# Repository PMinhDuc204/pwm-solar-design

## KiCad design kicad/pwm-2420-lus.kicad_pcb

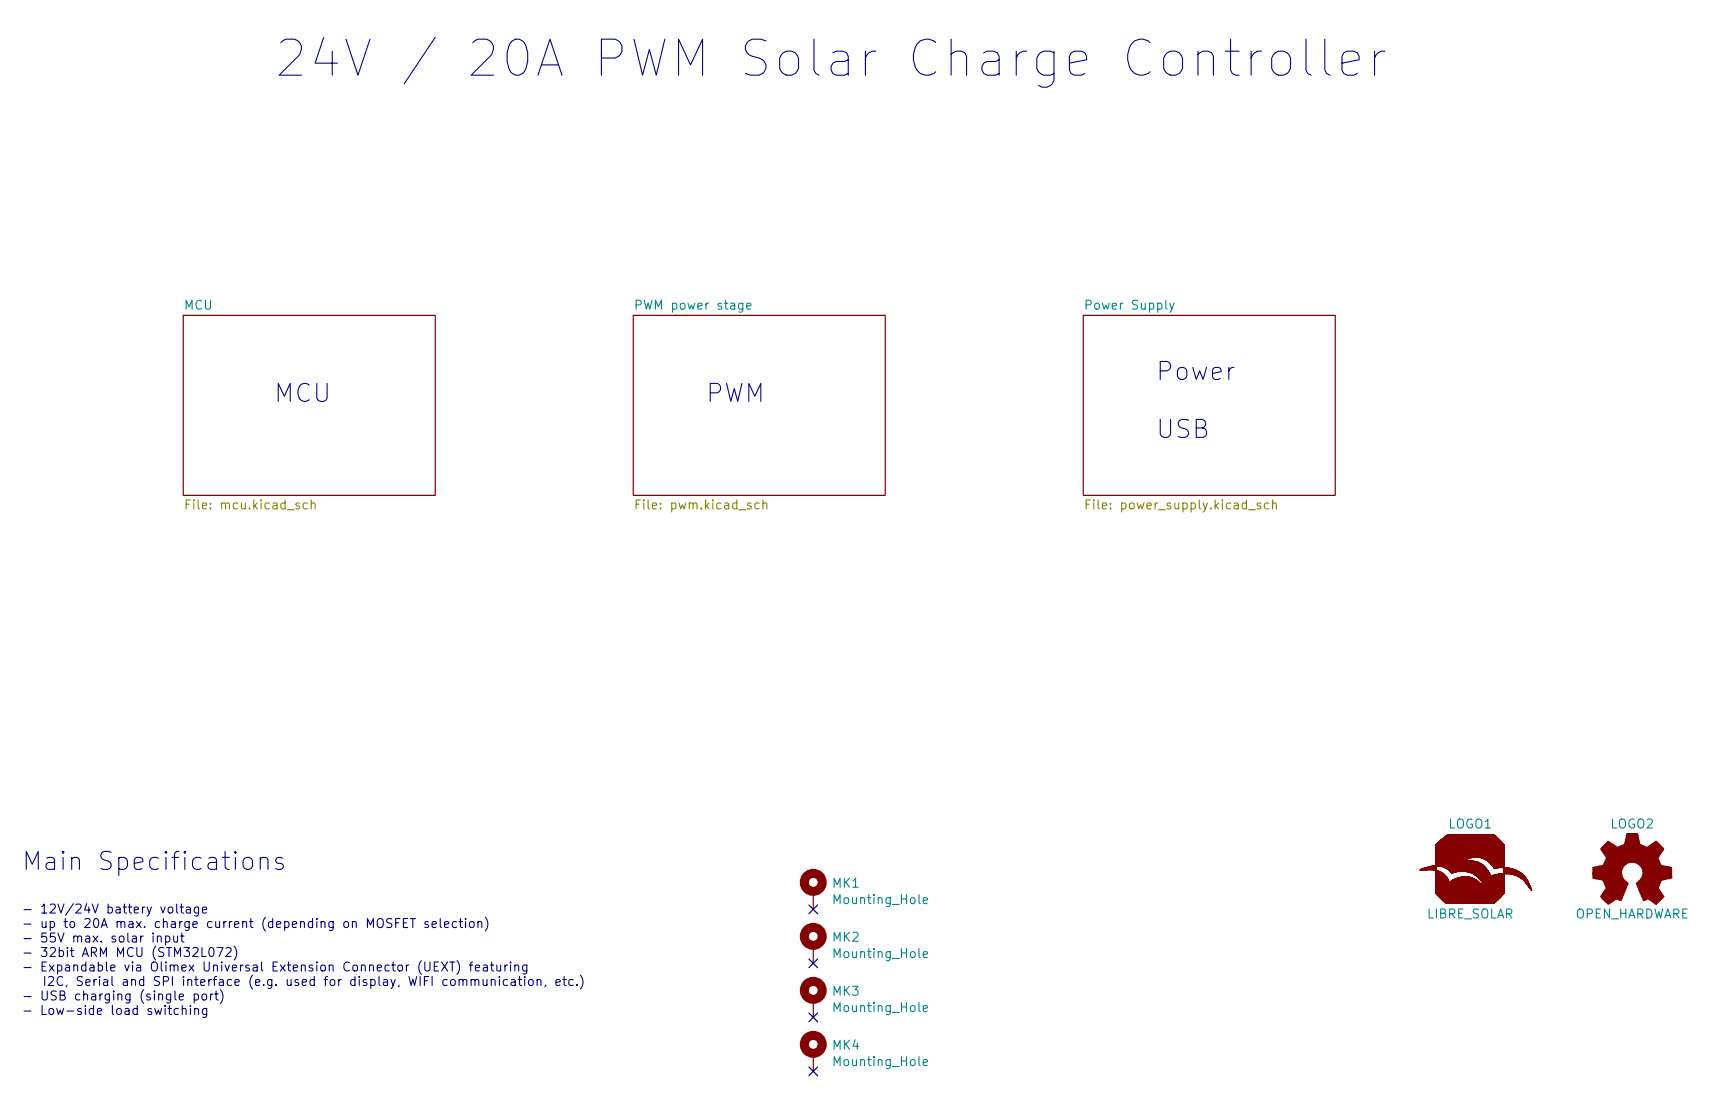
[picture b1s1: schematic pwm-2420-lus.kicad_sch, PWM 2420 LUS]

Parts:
LOGO1: LIBRE_SOLAR; LIBRESOLAR_LOGO
LOGO2: OPEN_HARDWARE; OSHW-Logo_5.7x6mm_SilkScreen
MK1, MK2, MK3, MK4: Mounting_Hole; MountingHole_3.2mm_M3_Pad

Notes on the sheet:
MCU
Main Specifications
24V / 20A PWM Solar Charge Controller
PWM
- 12V/24V battery voltage - up to 20A max. charge current (depending on MOSFET selection) - 55V max. solar input - 32bit ARM MCU (STM32L072) - Expandable via Olimex Universal Extension Connector (UEXT) featuring I2C, Serial and SPI interface (e.g. used for display, WIFI communication, etc.) - USB c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
Power USB

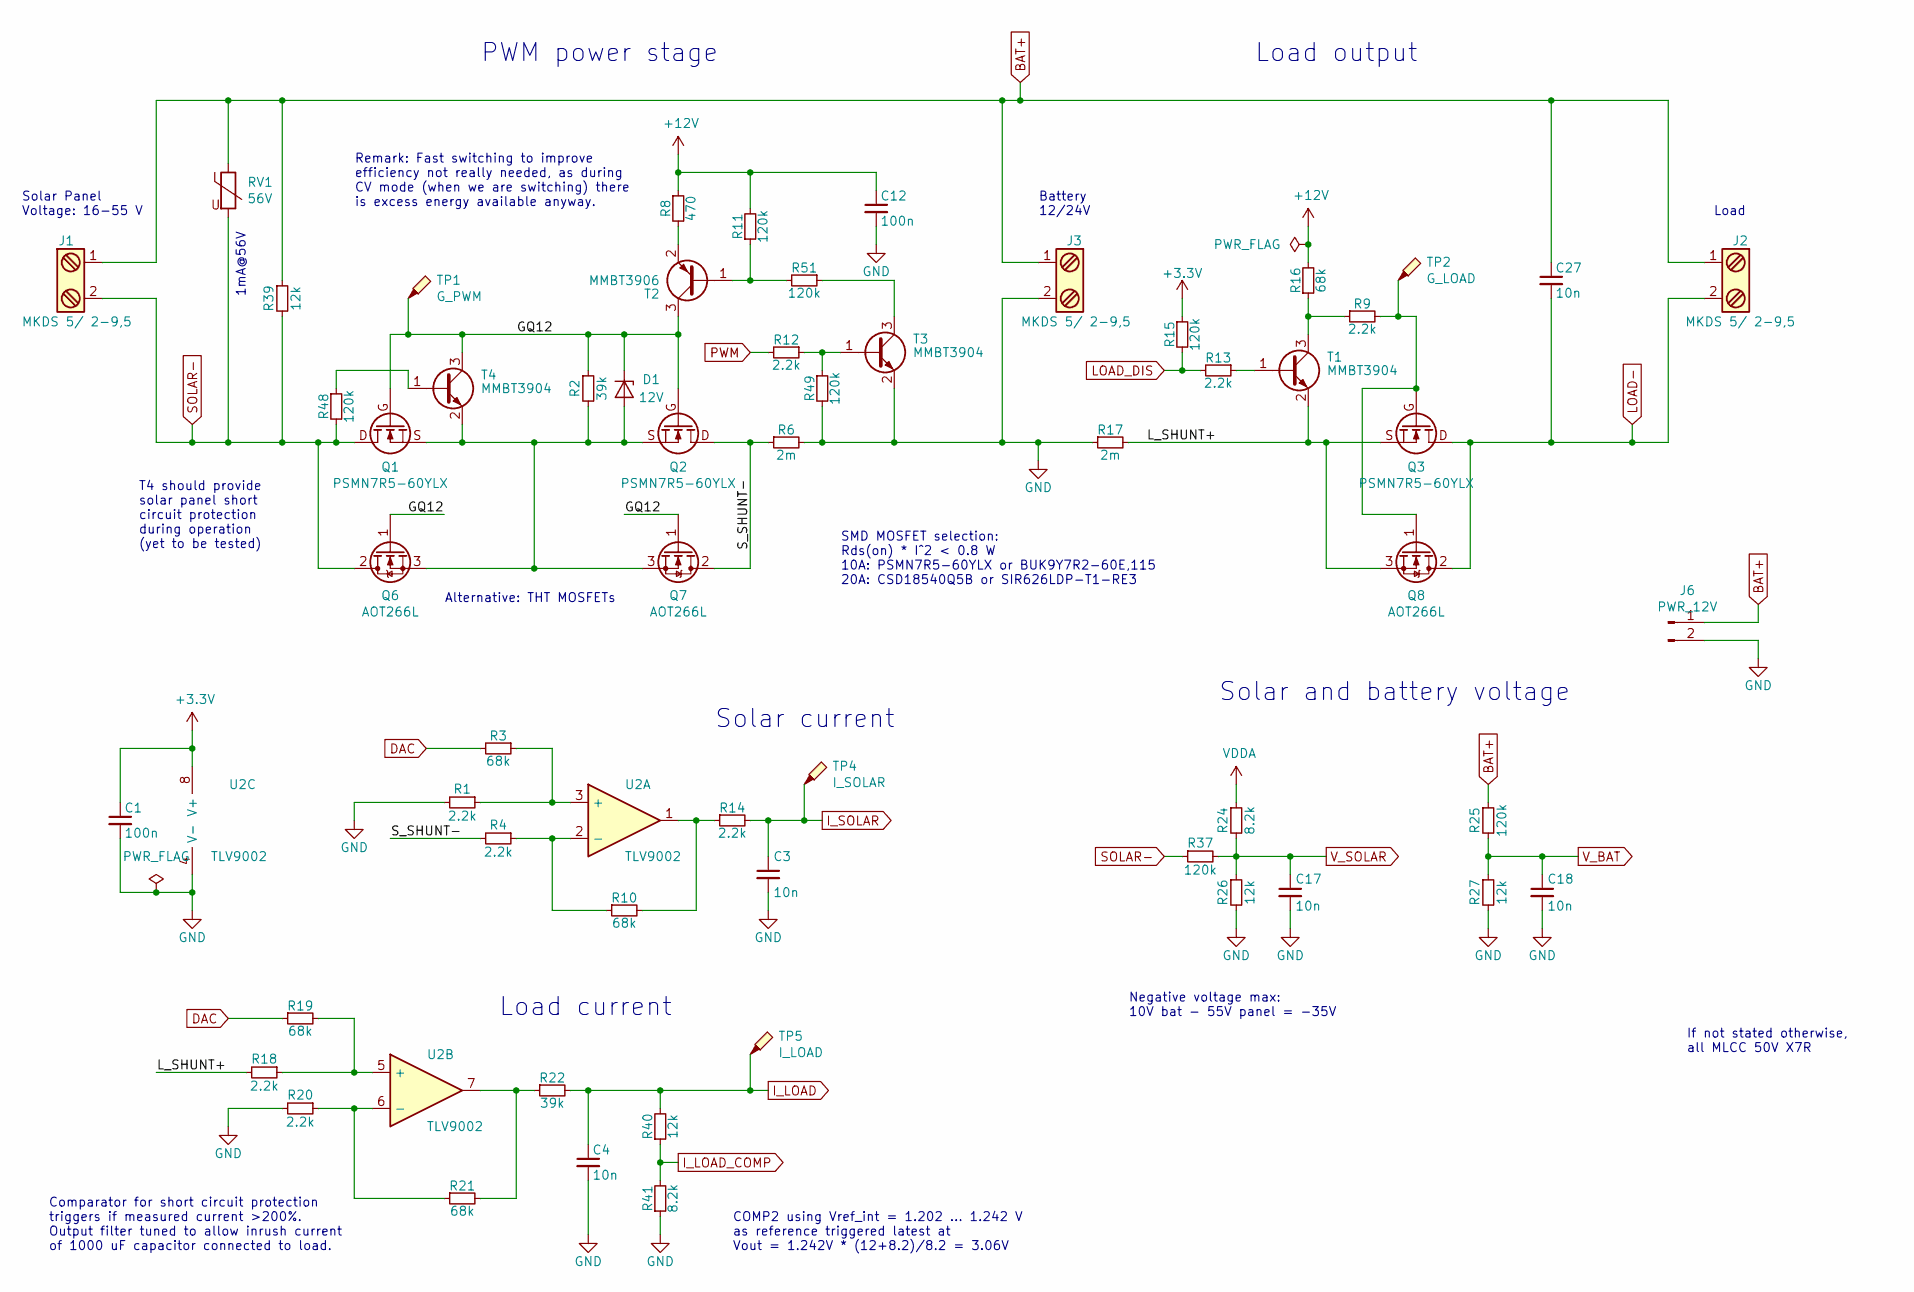
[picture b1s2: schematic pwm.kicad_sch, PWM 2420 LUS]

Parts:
C1, C12: 100n; C_0805_2012; PartNumber CC0805KRX7R9BB104
C3, C4, C17, C18, C27: 10n; C_0805_2012; PartNumber CC0805KRX7R0BB103
D1: 12V; D_SOT-23_ANK; PartNumber SZBZX84C12LT3G
J1, J2, J3: MKDS 5/ 2-9,5; Phoenix_Contact_MKDS_5-2-952; PartNumber 1714971
J6: PWR_12V; JST_XH_B2B-XH-A_1x02_P2.50mm_Vertical; PartNumber B2B-XH-A (LF)(SN)
Q1, Q2, Q3: PSMN7R5-60YLX; 5X6_MOSFET; PartNumber PSMN7R5-60YLX
Q6, Q7, Q8: AOT266L; TO-220-3_Horizontal_TabUp; PartNumber AOT266L
R1, R4, R9, R12, R13, R14, R18, R20: 2.2k; R_0805_2012; PartNumber RC0805FR-072K2L
R2: 39k; R_0805_2012; PartNumber RC0805FR-0739KL
R3, R10, R16, R19, R21: 68k; R_0805_2012; PartNumber RC0805FR-0768KL
R6, R17: 2m; R_Bourns_CRE2512; PartNumber CRE2512-FZ-R002E-3
R8: 470; R_0805_2012; PartNumber RC0805FR-07470RL
R11, R15, R25, R37, R48, R49, R51: 120k; R_0805_2012; PartNumber RC0805FR-07120KL
R22: 39k; R_0805_2012; PartNumber RC0805FR-0739K0L
R24, R41: 8.2k; R_0805_2012; PartNumber RC0805FR-078K2L
R26, R27, R39, R40: 12k; R_0805_2012; PartNumber RC0805FR-0712KL
RV1: 56V; RV_Disc_D12mm_W4.3mm_P7.5mm; PartNumber MOV-10D560K
T1, T3, T4: MMBT3904; SOT-23; PartNumber MMBT3904-7-F
T2: MMBT3906; SOT-23; PartNumber MMBT3906-7-F
TP1: G_PWM; TestPoint_Pad_D1.0mm
TP2: G_LOAD; TestPoint_Pad_D1.0mm
TP4: I_SOLAR; TestPoint_Pad_D1.0mm
TP5: I_LOAD; TestPoint_Pad_D1.0mm
U2: TLV9002; SOIC-8_3.9x4.9mm_Pitch1.27mm; PartNumber LM258DR

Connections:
+3V3: C1.1, R15.1, U2.8 (V+); also elsewhere on the board
+12V: C12.1, R8.1, R11.2, R16.2; also elsewhere on the board
/PWM power stage/GQ12: D1.1 (K), Q1.G, Q2.G, Q6.1 (G), Q7.1 (G), R2.1, T2.3 (C), T4.3 (C), TP1.1
/PWM power stage/L_SHUNT+: Q3.S, Q8.3 (S), R17.2, R18.2, T1.2 (E)
/PWM power stage/S_SHUNT-: Q2.D, Q7.2 (D), R4.2, R6.1
BAT+: C27.1, J1.1, J2.1, J3.1, J6.1, R25.1, R39.1, RV1.1; also elsewhere on the board
DAC: R3.2, R19.1; also elsewhere on the board
GND: C1.2, C3.2, C4.2, C12.2, C17.2, C18.2, J3.2, J6.2, R1.2, R6.2, R17.1, R20.2, R26.2, R27.2, R41.1, R49.2, T3.2 (E), U2.4 (V-); also elsewhere on the board
I_LOAD: C4.1, R22.2, R40.2, TP5.1; also elsewhere on the board
I_LOAD_COMP: R40.1, R41.2; also elsewhere on the board
I_SOLAR: C3.1, R14.2, TP4.1; also elsewhere on the board
LOAD-: C27.2, J2.2, Q3.D, Q8.2 (D); also elsewhere on the board
LOAD_DIS: R13.2, R15.2; also elsewhere on the board
unnamed: D1.2 (A), Q1.S, Q2.S, Q6.3 (S), Q7.3 (S), R2.2, T4.2 (E)
unnamed: Q3.G, Q8.1 (G), R9.2, TP2.1
unnamed: R1.1, R3.1, U2.3 (+)
unnamed: R8.2, T2.2 (E)
unnamed: R4.1, R10.1, U2.2 (-)
unnamed: R10.2, R14.1, U2.1
unnamed: R11.1, R51.2, T2.1 (B)
unnamed: R12.1, R49.1, T3.1 (B)
unnamed: R13.1, T1.1 (B)
unnamed: R9.1, R16.1, T1.3 (C)
unnamed: R18.1, R19.2, U2.5 (+)
unnamed: R20.1, R21.1, U2.6 (-)
unnamed: R21.2, R22.1, U2.7
unnamed: R48.1, T4.1 (B)
unnamed: R51.1, T3.3 (C)
PWM: R12.2; also elsewhere on the board
SOLAR-: J1.2, Q1.D, Q6.2 (D), R37.1, R39.2, R48.2, RV1.2
VDDA: R24.1; also elsewhere on the board
V_BAT: C18.1, R25.2, R27.1; also elsewhere on the board
V_SOLAR: C17.1, R24.2, R26.1, R37.2; also elsewhere on the board

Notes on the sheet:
Solar current
Comparator for short circuit protection triggers if measured current >200%. Output filter tuned to allow inrush current of 1000 uF capacitor connected to load.
Solar and battery voltage
Load current
Load
Remark: Fast switching to improve efficiency not really needed, as during CV mode (when we are switching) there is excess energy available anyway.
SMD MOSFET selection: Rds(on) * I^2 < 0.8 W 10A: PSMN7R5-60YLX or BUK9Y7R2-60E,115 20A: CSD18540Q5B or SIR626LDP-T1-RE3
Battery 12/24V
Load output
Solar Panel Voltage: 16-55 V
1mA@56V
PWM power stage
Negative voltage max: 10V bat - 55V panel = -35V
COMP2 using Vref_int = 1.202 ... 1.242 V as reference triggered latest at Vout = 1.242V * (12+8.2)/8.2 = 3.06V
T4 should provide solar panel short circuit protection during operation (yet to be tested)
If not stated otherwise, all MLCC 50V X7R
Alternative: THT MOSFETs

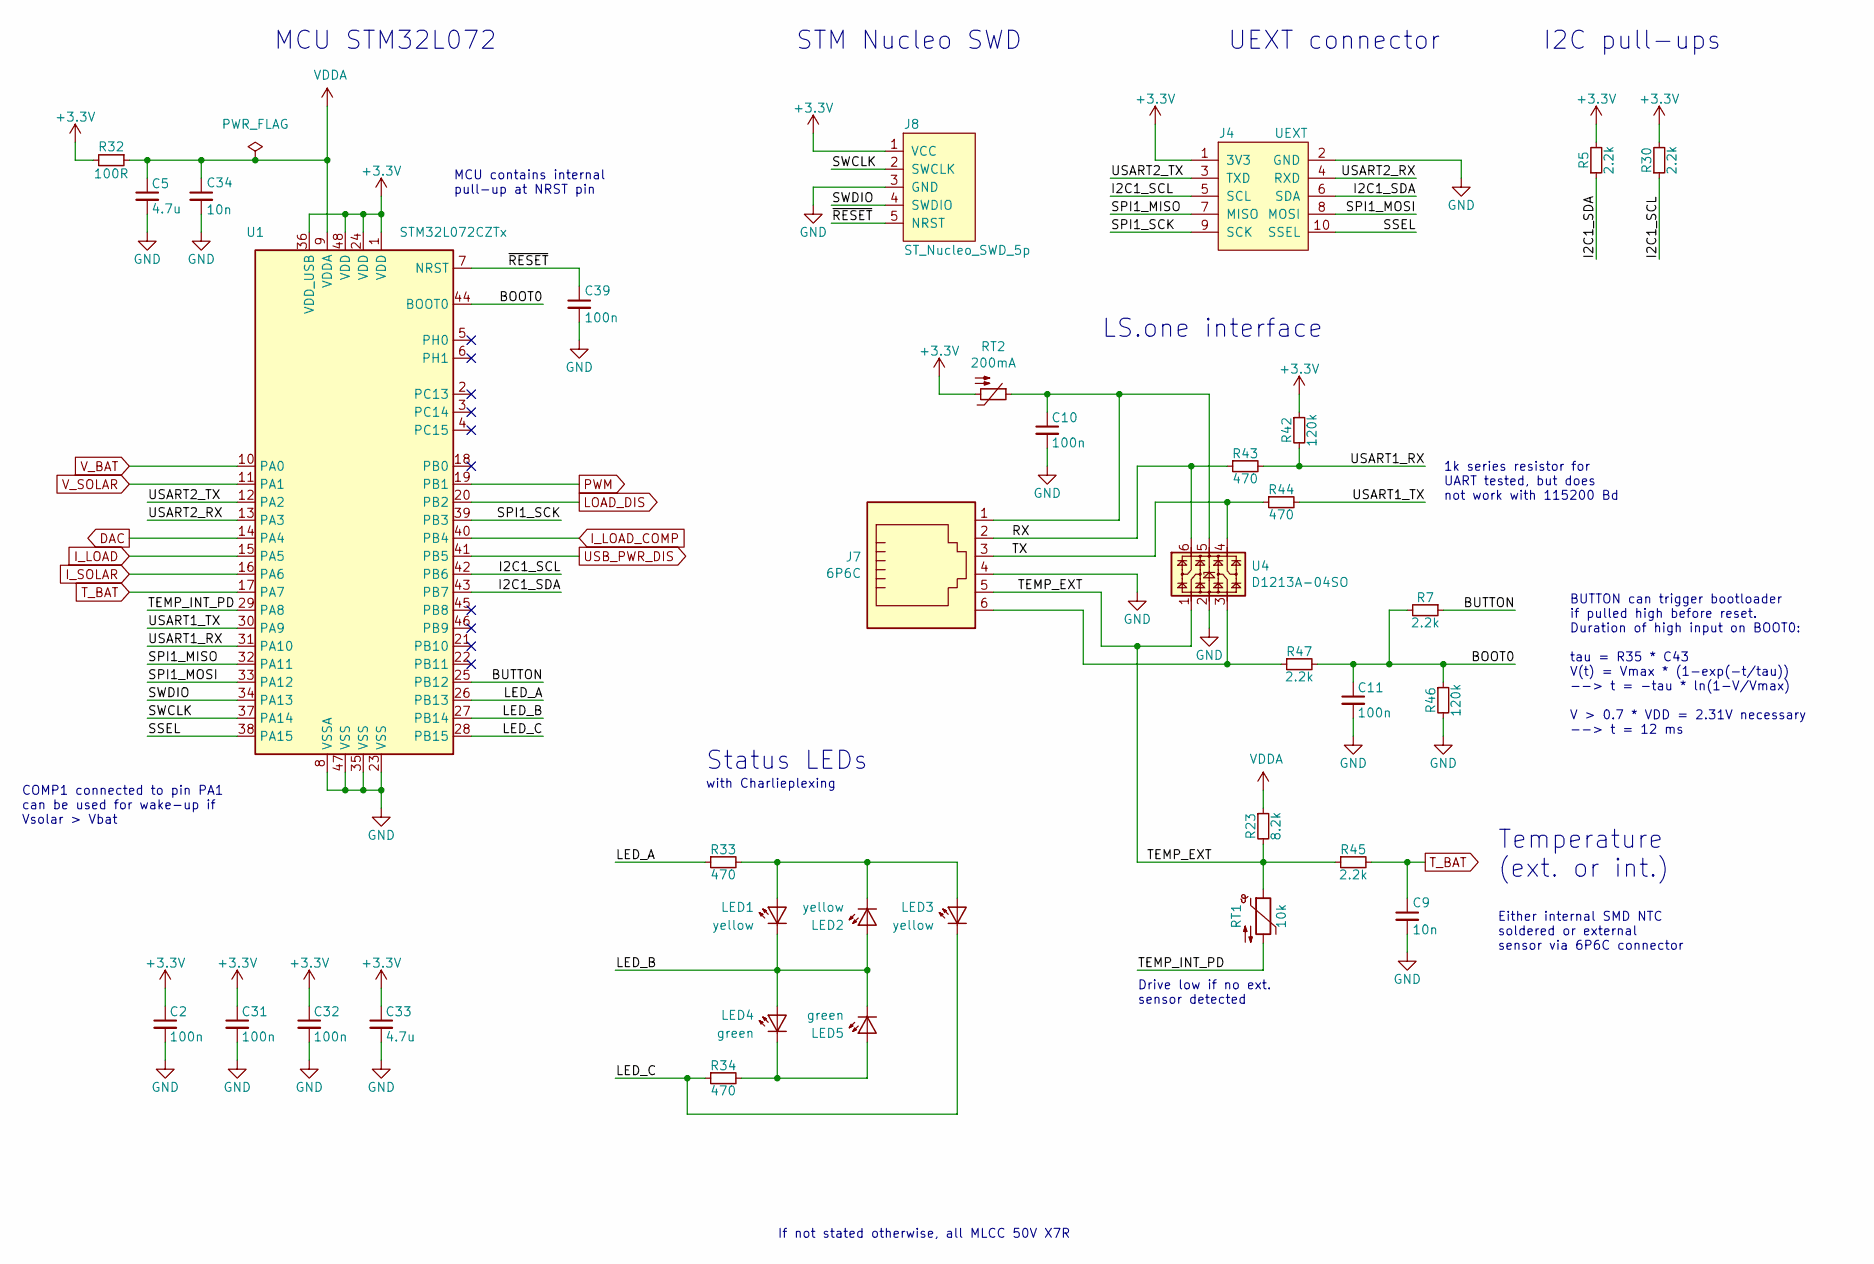
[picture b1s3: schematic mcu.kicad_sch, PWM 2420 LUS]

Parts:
C2, C10, C11, C31, C32, C39: 100n; C_0805_2012; PartNumber CC0805KRX7R9BB104
C5, C33: 4.7u; C_0805_2012; PartNumber 885012107018
C9, C34: 10n; C_0805_2012; PartNumber CC0805KRX7R0BB103
J4: UEXT; Box_Header_2x05x2.54mm_Straight; PartNumber 302-S101
J7: 6P6C; RJ25_6P6C_TabUp; PartNumber 615006138421
J8: ST_Nucleo_SWD_5p; PinHeader_1x05_P2.54mm_Vertical
LED1, LED2, LED3: yellow; LED_0603_D3.0mm; PartNumber LTL-1CHY
LED4, LED5: green; LED_0603_D3.0mm; PartNumber LTL-4231
R5, R7, R30, R45, R47: 2.2k; R_0805_2012; PartNumber RC0805FR-072K2L
R23: 8.2k; R_0805_2012; PartNumber RC0805FR-078K2L
R32: 100R; R_0805_2012; PartNumber RC0805FR-07100RL
R33, R34, R43, R44: 470; R_0805_2012; PartNumber RC0805FR-07470RL
R42, R46: 120k; R_0805_2012; PartNumber RC0805FR-07120KL
RT1: 10k; R_0805_2012; PartNumber NCP21XV103J03RA
RT2: 200mA; R_1206_3216; PartNumber 0ZCJ0020FF2E
U1: STM32L072CZTx; LQFP-48_7x7mm_P0.5mm; PartNumber STM32L072CZT6
U4: D1213A-04SO; SOT-23-6; PartNumber D1213A-04SO

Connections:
+3V3: C2.1, C31.1, C32.1, C33.1, J4.1 (3V3), J8.1 (VCC), R5.2, R30.2, R32.2, R42.1, RT2.2, U1.1 (VDD), U1.24 (VDD), U1.36 (VDD_USB), U1.48 (VDD); also elsewhere on the board
/MCU/BOOT0: C11.1, R7.2, R46.1, R47.2, U1.44 (BOOT0)
/MCU/BUTTON: R7.1, U1.25 (PB12)
/MCU/I2C1_SCL: J4.5 (SCL), R30.1, U1.42 (PB6)
/MCU/I2C1_SDA: J4.6 (SDA), R5.1, U1.43 (PB7)
/MCU/LED_A: R33.1, U1.26 (PB13)
/MCU/LED_B: LED1.1 (K), LED2.2 (A), LED4.2 (A), LED5.1 (K), U1.27 (PB14)
/MCU/LED_C: LED3.1 (K), R34.1, U1.28 (PB15)
/MCU/RX: J7.2, R43.1, U4.6
/MCU/SPI1_MISO: J4.7 (MISO), U1.32 (PA11)
/MCU/SPI1_MOSI: J4.8 (MOSI), U1.33 (PA12)
/MCU/SPI1_SCK: J4.9 (SCK), U1.39 (PB3)
/MCU/SSEL: J4.10 (SSEL), U1.38 (PA15)
/MCU/SWCLK: J8.2 (SWCLK), U1.37 (PA14)
/MCU/SWDIO: J8.4 (SWDIO), U1.34 (PA13)
/MCU/TEMP_EXT: J7.5, R23.2, R45.1, RT1.1, U4.1
/MCU/TEMP_INT_PD: RT1.2, U1.29 (PA8)
/MCU/TX: J7.3, R44.1, U4.4
/MCU/USART1_RX: R42.2, R43.2, U1.31 (PA10)
/MCU/USART1_TX: R44.2, U1.30 (PA9)
/MCU/USART2_RX: J4.4 (RXD), U1.13 (PA3)
/MCU/USART2_TX: J4.3 (TXD), U1.12 (PA2)
/MCU/~RESET: C39.1, J8.5 (NRST), U1.7 (NRST)
DAC: U1.14 (PA4); also elsewhere on the board
GND: C2.2, C5.2, C9.2, C10.2, C11.2, C31.2, C32.2, C33.2, C34.2, C39.2, J4.2 (GND), J7.4, J8.3 (GND), R46.2, U1.8 (VSSA), U1.23 (VSS), U1.35 (VSS), U1.47 (VSS), U4.2; also elsewhere on the board
I_LOAD: U1.15 (PA5); also elsewhere on the board
I_LOAD_COMP: U1.40 (PB4); also elsewhere on the board
I_SOLAR: U1.16 (PA6); also elsewhere on the board
LOAD_DIS: U1.20 (PB2); also elsewhere on the board
unnamed: C10.1, J7.1, RT2.1, U4.5
unnamed: J7.6, R47.1, U4.3
unnamed: LED1.2 (A), LED2.1 (K), LED3.2 (A), R33.2
unnamed: LED4.1 (K), LED5.2 (A), R34.2
PWM: U1.19 (PB1); also elsewhere on the board
T_BAT: C9.1, R45.2, U1.17 (PA7)
USB_PWR_DIS: U1.41 (PB5); also elsewhere on the board
VDDA: C5.1, C34.1, R23.1, R32.1, U1.9 (VDDA); also elsewhere on the board
V_BAT: U1.10 (PA0); also elsewhere on the board
V_SOLAR: U1.11 (PA1); also elsewhere on the board

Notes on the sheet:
MCU STM32L072
COMP1 connected to pin PA1 can be used for wake-up if Vsolar > Vbat
LS.one interface
Drive low if no ext. sensor detected
Temperature (ext. or int.)
with Charlieplexing
BUTTON can trigger bootloader if pulled high before reset. Duration of high input on BOOT0: tau = R35 * C43 V(t) = Vmax * (1-exp(-t/tau)) --> t = -tau * ln(1-V/Vmax) V > 0.7 * VDD = 2.31V necessary --> t = 12 ms
UEXT connector
MCU contains internal pull-up at NRST pin
Status LEDs
I2C pull-ups
1k series resistor for UART tested, but does not work with 115200 Bd
STM Nucleo SWD
Either internal SMD NTC soldered or external sensor via 6P6C connector
If not stated otherwise, all MLCC 50V X7R

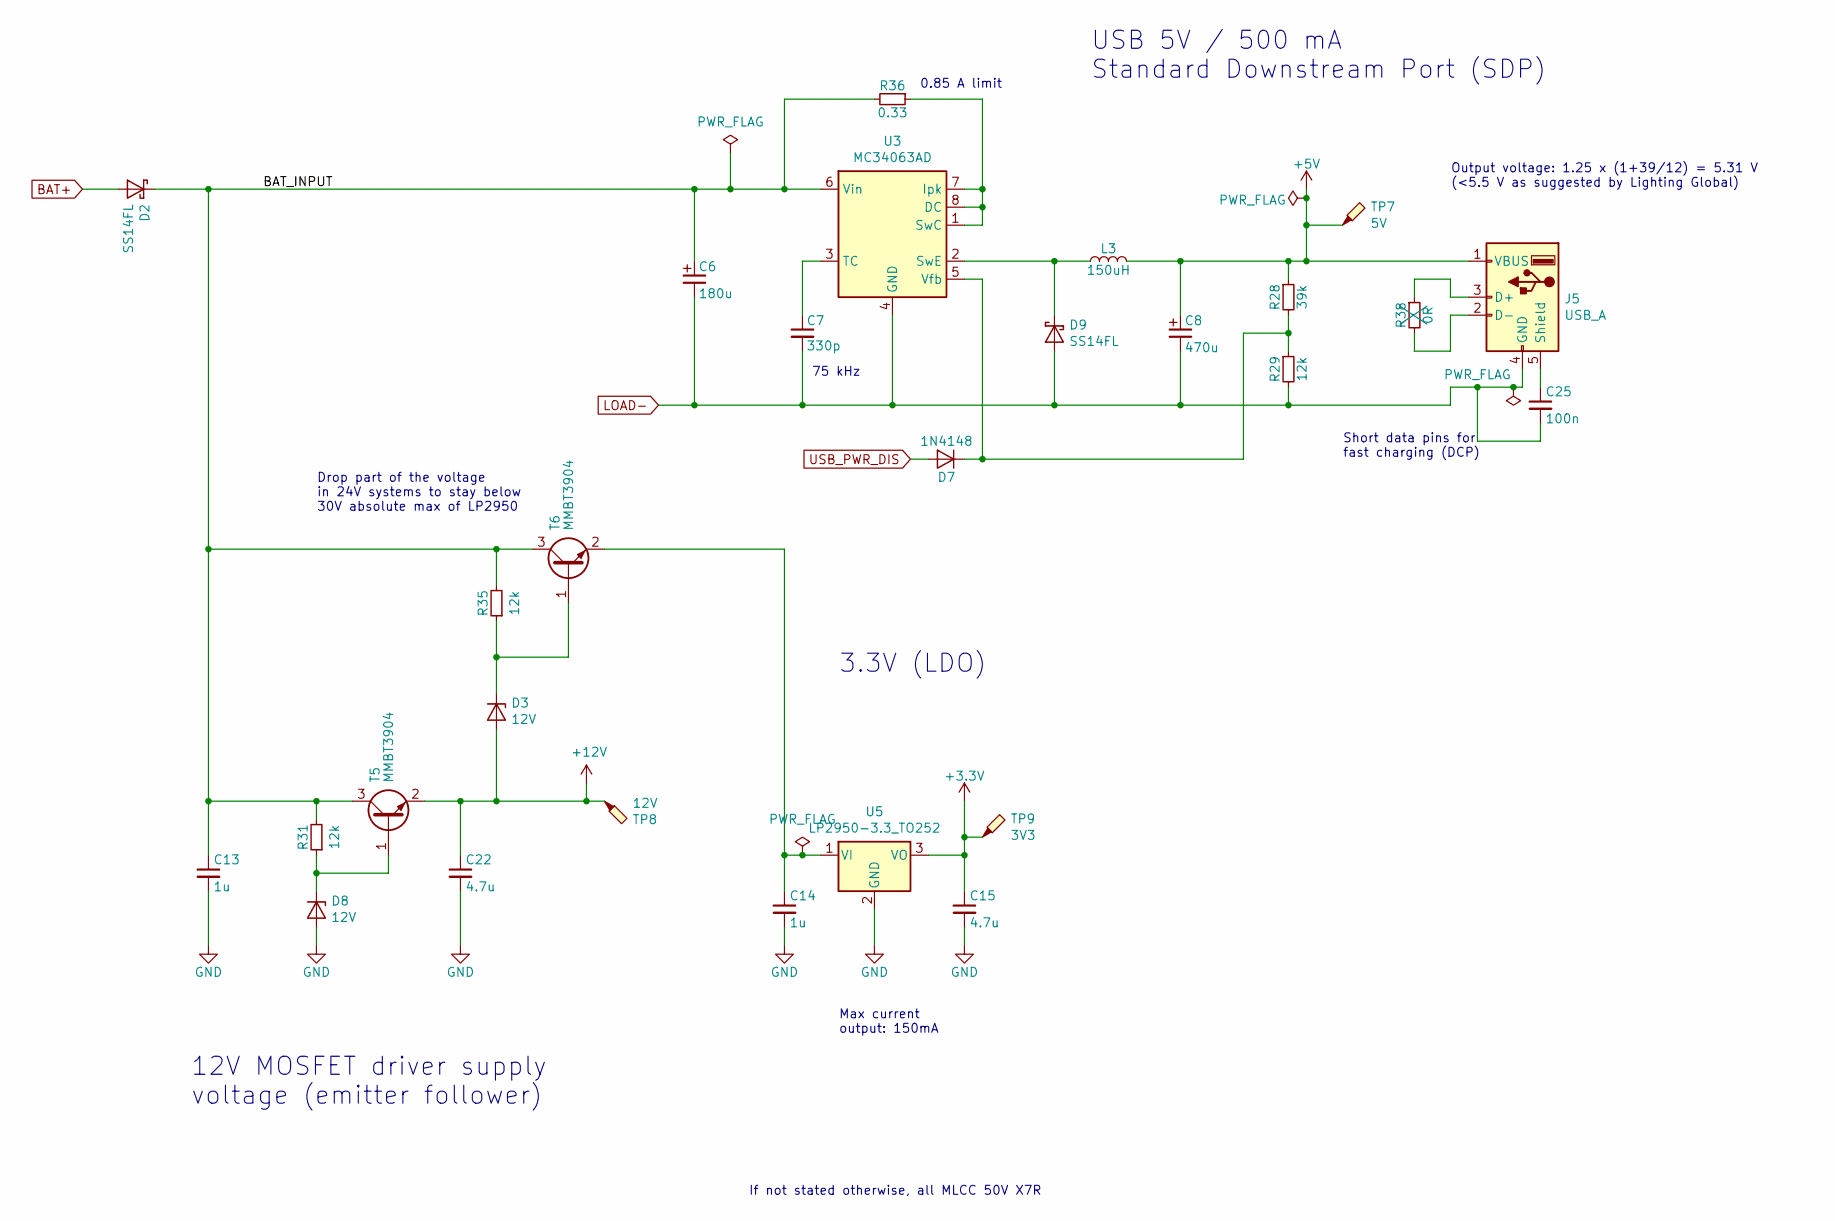
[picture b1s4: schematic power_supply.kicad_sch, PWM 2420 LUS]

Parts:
C6: 180u; CP_Radial_D8.0mm_P3.50mm; PartNumber EEU-FR1V181
C7: 330p; C_0805_2012; PartNumber 885342007002
C8: 470u; CP_Radial_D8.0mm_P3.50mm; PartNumber EEUFR1A471
C13, C14: 1u; C_0805_2012; PartNumber CC0805KKX7R9BB105
C15, C22: 4.7u; C_0805_2012; PartNumber 885012107018
C25: 100n; C_0805_2012; PartNumber CC0805KRX7R9BB104
D2, D9: SS14FL; D_SOD-123F; PartNumber SS14FL
D3, D8: 12V; D_SOT-23_ANK; PartNumber SZBZX84C12LT3G
D7: 1N4148; D_SOD-123; PartNumber 1N4148W-7-F
J5: USB_A; USB_A_Wuerth_61400416021_Horizontal; PartNumber 61400416021
L3: 150uH; L_Radial_D12.0mm_P5.00mm_Fastron_11P; PartNumber RLB0914-151KL
R28: 39k; R_0805_2012; PartNumber RC0805FR-0739KL
R29, R31, R35: 12k; R_0805_2012; PartNumber RC0805FR-0712KL
R36: 0.33; R_1206_3216; PartNumber RL1206FR-070R33L
R38: 0R; R_0805_2012; PartNumber RC0805FR-070RL
T5, T6: MMBT3904; SOT-23; PartNumber MMBT3904-7-F
TP7: 5V; TestPoint_Pad_D1.0mm
TP8: 12V; TestPoint_Pad_D1.0mm
TP9: 3V3; TestPoint_Pad_D1.0mm
U3: MC34063AD; SOIC-8_3.9x4.9mm_P1.27mm; PartNumber MC34063ADR
U5: LP2950-3.3_TO252; TO-252-2; PartNumber LP2950ACDT-3.3RG

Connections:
+3V3: C15.1, TP9.1, U5.3 (VO); also elsewhere on the board
+5V: C8.1, J5.1 (VBUS), L3.2, R28.1, TP7.1
+12V: C22.1, D3.2 (A), T5.2 (E), TP8.1; also elsewhere on the board
/Power Supply/BAT_INPUT: C6.1, C13.1, D2.1 (K), R31.2, R35.2, R36.2, T5.3 (C), T6.3 (C), U3.6 (Vin)
BAT+: D2.2 (A); also elsewhere on the board
GND: C13.2, C14.2, C15.2, C22.2, D8.2 (A), U5.2 (GND); also elsewhere on the board
LOAD-: C6.2, C7.2, C8.2, C25.2, D9.2 (A), J5.4 (GND), R29.2, U3.4 (GND); also elsewhere on the board
unnamed: C7.1, U3.3 (TC)
unnamed: C14.1, T6.2 (E), U5.1 (VI)
unnamed: C25.1, J5.5 (Shield)
unnamed: D3.1 (K), R35.1, T6.1 (B)
unnamed: D7.1 (K), R28.2, R29.1, U3.5 (Vfb)
unnamed: D8.1 (K), R31.1, T5.1 (B)
unnamed: D9.1 (K), L3.1, U3.2 (SwE)
unnamed: J5.2 (D-), R38.2
unnamed: J5.3 (D+), R38.1
unnamed: R36.1, U3.1 (SwC), U3.7 (Ipk), U3.8 (DC)
USB_PWR_DIS: D7.2 (A); also elsewhere on the board

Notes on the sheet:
0.85 A limit
Max current output: 150mA
USB 5V / 500 mA Standard Downstream Port (SDP)
Drop part of the voltage in 24V systems to stay below 30V absolute max of LP2950
3.3V (LDO)
12V MOSFET driver supply voltage (emitter follower)
If not stated otherwise, all MLCC 50V X7R
Short data pins for fast charging (DCP)
75 kHz
Output voltage: 1.25 x (1+39/12) = 5.31 V (<5.5 V as suggested by Lighting Global)

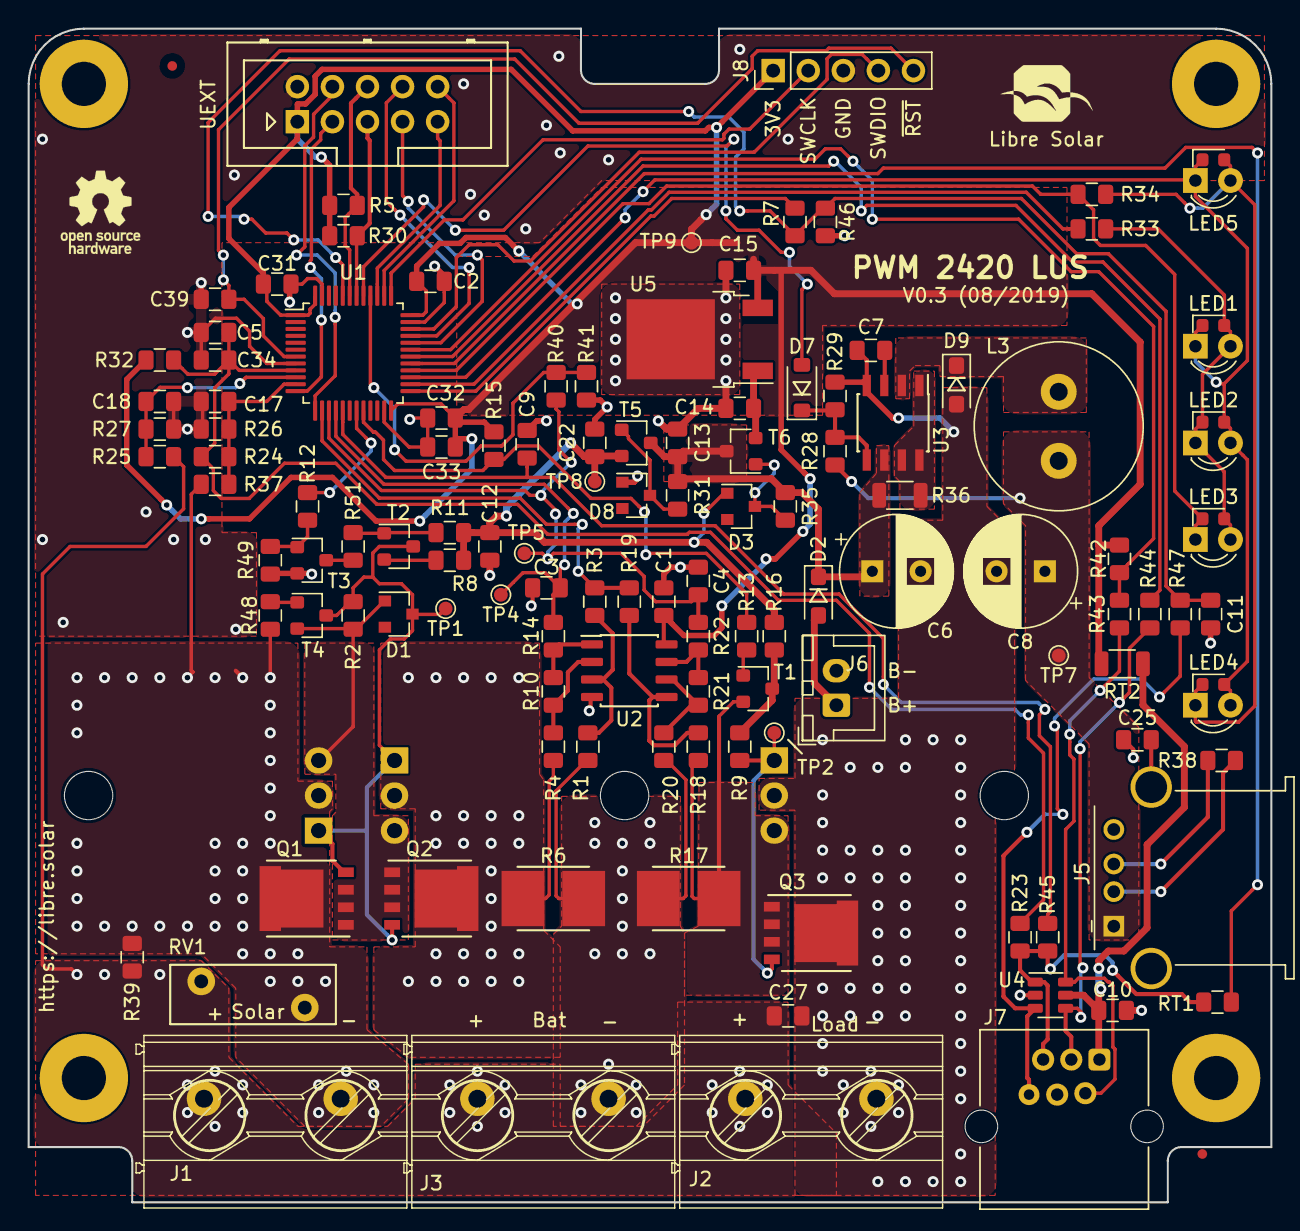
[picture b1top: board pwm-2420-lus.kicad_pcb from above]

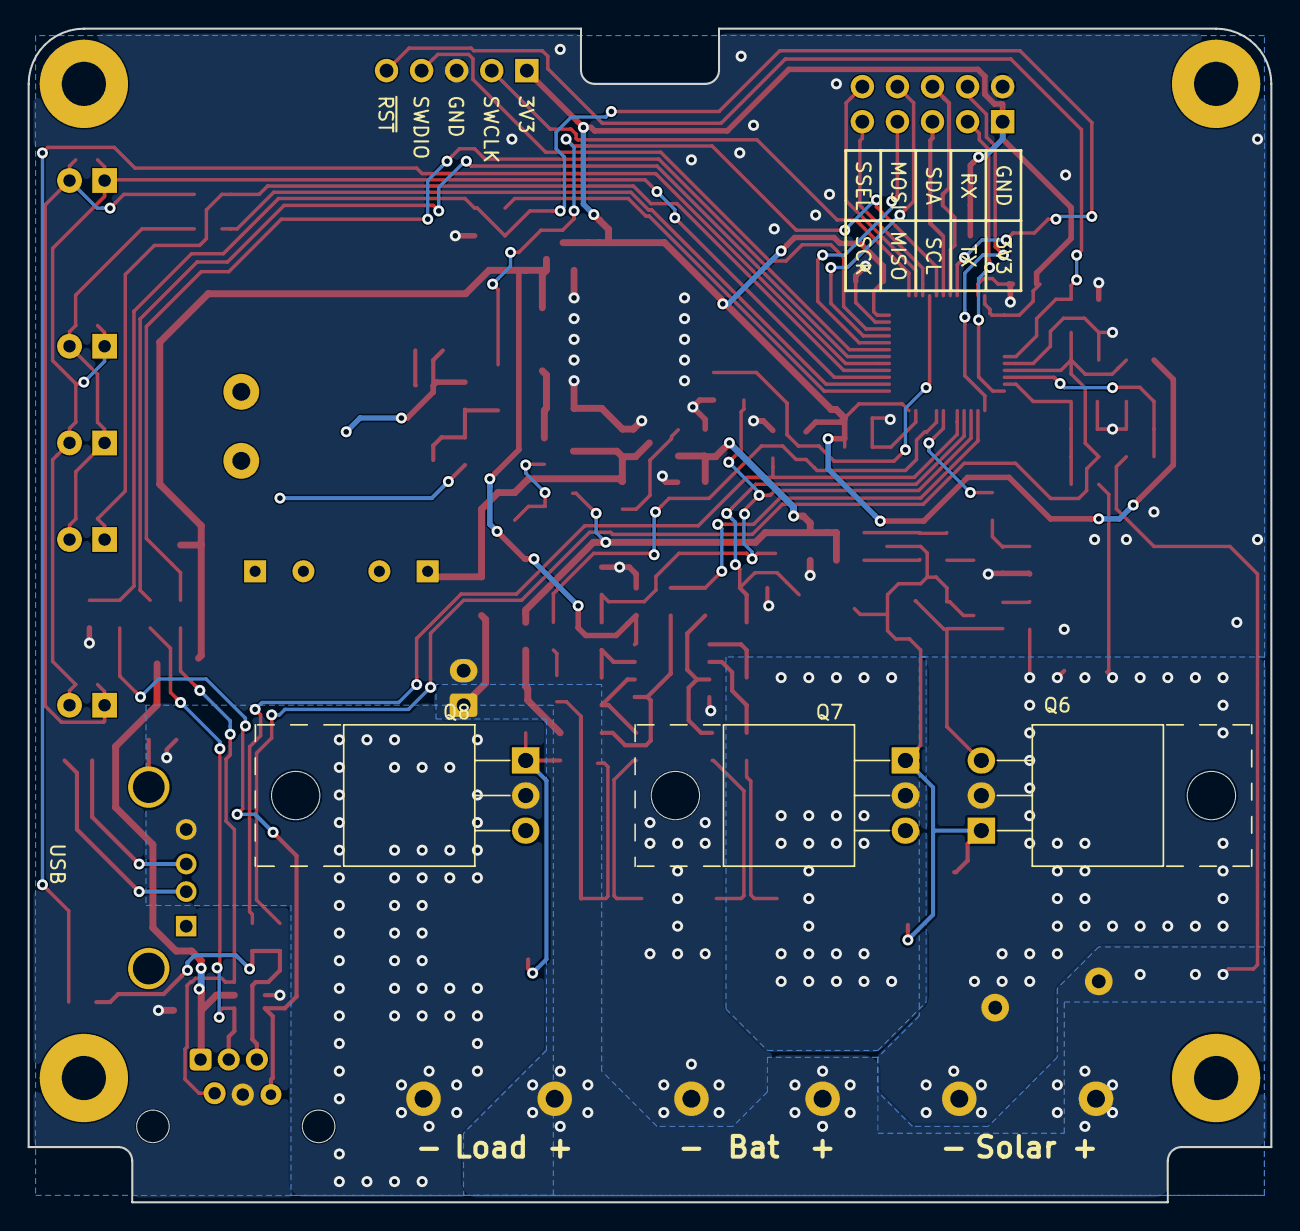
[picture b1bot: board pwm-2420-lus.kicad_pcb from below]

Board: 2 copper layers, 90.0 x 85.0 mm, 128 parts (3 on the bottom side), 73 nets.
